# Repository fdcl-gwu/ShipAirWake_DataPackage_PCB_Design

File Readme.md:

# PCB_Design_Two_Anemometers

PCB .sch & .brd files.
Designed using EagleCAD.

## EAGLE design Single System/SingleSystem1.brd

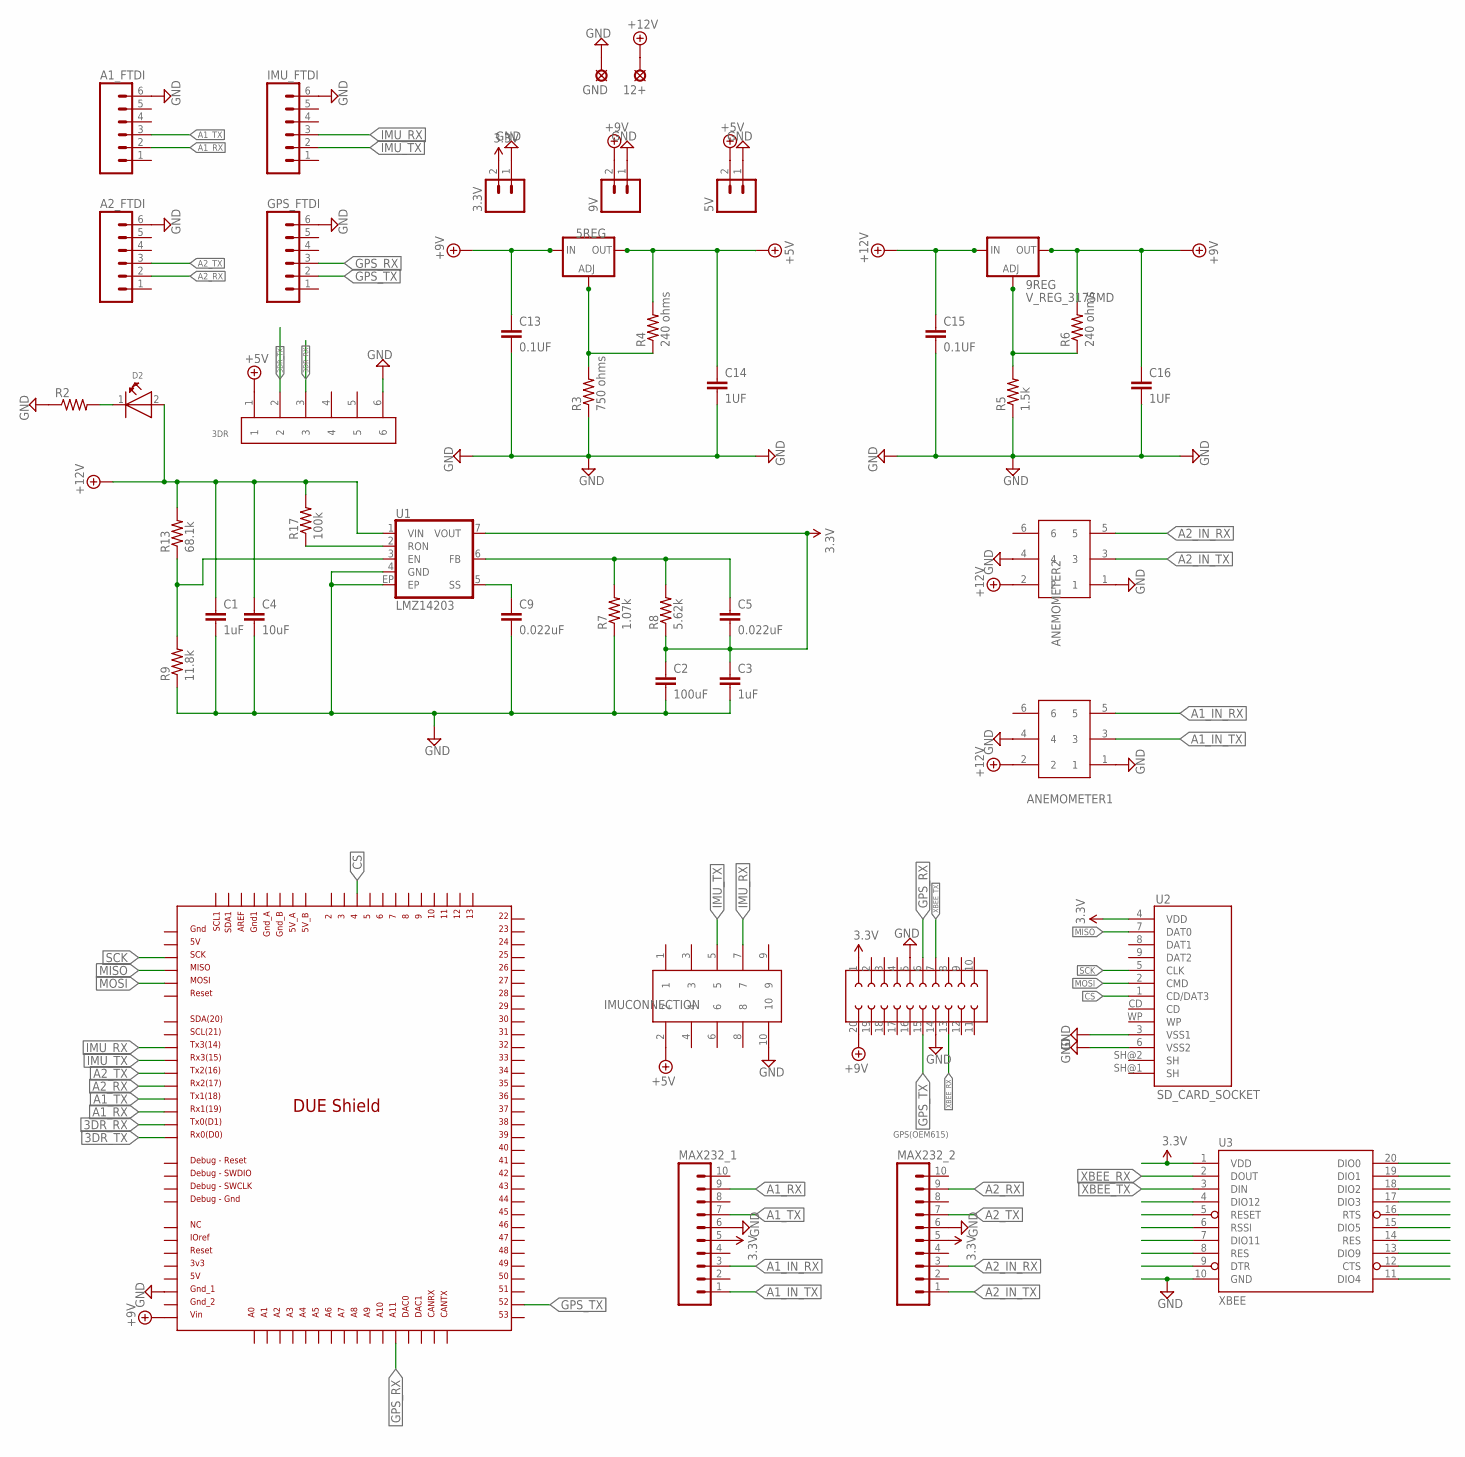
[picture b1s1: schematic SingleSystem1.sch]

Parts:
3.3V, 5V, 9V: M02; 02P
3DR: 653006114822
5REG, 9REG: V_REG_317SMD; SOT223
12+: SE14
A1_FTDI, A2_FTDI: M06; 06P
ANEMOMETER1, ANEMOMETER2: 61200622323
C1, C3: 1uF; 0805; MPN 1C10Z5U104M050R
C2: 100uF; 1206
C4: 10uF; 0805
C5, C9: 0.022uF; 0603-CAP
C13, C15: 0.1UF; 0805
C14, C16: 1UF; 0805
D2: WL-SMCW-150120BS75000-B; 1206
GND: SE14
GPS(OEM615): 62002021821
GPS_FTDI: M06; 06P
IMUCONNECTION: 62501021621
IMU_FTDI: M06; 06P
MAX232_1, MAX232_2: M10; 10P
R2: R-US_M2012; M2012
R3: 750 ohms; M2012
R4, R6: 240 ohms; M2012
R5: 1.5k; M2012
R7: 1.07k; M2012
R8: 5.62k; M2012
R9: 11.8k; M2012
R13: 68.1k; M2012
R17: 100k; M2012
U1: LMZ14203; TO-PMOD-7
U2: SD_CARD_SOCKET; SD_1:1
U3: XBEE; XBEE-1
U$1: DUE(NORMAL)

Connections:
3.3V: 3.3V.2, C2.1, C3.1, C5.2, GPS(OEM615).1, MAX232_1.5, MAX232_2.5, R8.1, U1.7 (VOUT), U2.4 (VDD), U3.1 (VDD)
3DR_RX: 3DR.3, U$1.TX0
3DR_TX: 3DR.2, U$1.RX0
+5V: 3DR.1, 5REG.2 (OUT), 5V.2, C14.1, IMUCONNECTION.2, R4.2
+9V: 5REG.3 (IN), 9REG.2 (OUT), 9V.2, C13.1, C16.1, GPS(OEM615).20, R6.2, U$1.VIN
+12V: 9REG.3 (IN), 12+.MP, ANEMOMETER1.2, ANEMOMETER2.2, C1.1, C4.1, C15.1, D2.2 (A), R13.2, R17.2, U1.1 (VIN)
A1_IN_RX: ANEMOMETER1.5, MAX232_1.3
A1_IN_TX: ANEMOMETER1.3, MAX232_1.1
A1_RX: A1_FTDI.2, MAX232_1.9, U$1.RX1
A1_TX: A1_FTDI.3, MAX232_1.7, U$1.TX1
A2_IN_RX: ANEMOMETER2.5, MAX232_2.3
A2_IN_TX: ANEMOMETER2.3, MAX232_2.1
A2_RX: A2_FTDI.2, MAX232_2.9, U$1.RX2
A2_TX: A2_FTDI.3, MAX232_2.7, U$1.TX2
CS: U2.1 (CD/DAT3), U$1.4
GND: 3.3V.1, 3DR.6, 5V.1, 9V.1, A1_FTDI.6, A2_FTDI.6, ANEMOMETER1.1, ANEMOMETER1.4, ANEMOMETER2.1, ANEMOMETER2.4, C1.2, C2.2, C3.2, C4.2, C9.2, C13.2, C14.2, C15.2, C16.2, GND.MP, GPS(OEM615).5, GPS(OEM615).14, GPS_FTDI.6, IMUCONNECTION.10, IMU_FTDI.6, MAX232_1.6, MAX232_2.6, R2.1, R3.1, R5.1, R7.1, R9.1, U1.4 (GND), U1.EP, U2.3 (VSS1), U2.6 (VSS2), U3.10 (GND), U$1.GND_1
GPS_RX: GPS(OEM615).6, GPS_FTDI.3, U$1.A11
GPS_TX: GPS(OEM615).15, GPS_FTDI.2, U$1.52
IMU_RX: IMUCONNECTION.7, IMU_FTDI.3, U$1.TX3
IMU_TX: IMUCONNECTION.5, IMU_FTDI.2, U$1.RX3
MISO: U2.7 (DAT0), U$1.MISO_ICSP
MOSI: U2.2 (CMD), U$1.MOSI_ICSP
unnamed: 5REG.1 (ADJ), R3.2, R4.1
unnamed: 9REG.1 (ADJ), R5.2, R6.1
unnamed: R9.2, R13.1, U1.3 (EN)
unnamed: R17.1, U1.2 (RON)
unnamed: C9.1, U1.5 (SS)
unnamed: D2.1 (K), R2.2
unnamed: C5.1, R7.2, R8.2, U1.6 (FB)
SCK: U2.5 (CLK), U$1.SCK_ICSP
XBEE_RX: GPS(OEM615).13, U3.2 (DOUT)
XBEE_TX: GPS(OEM615).7, U3.3 (DIN)

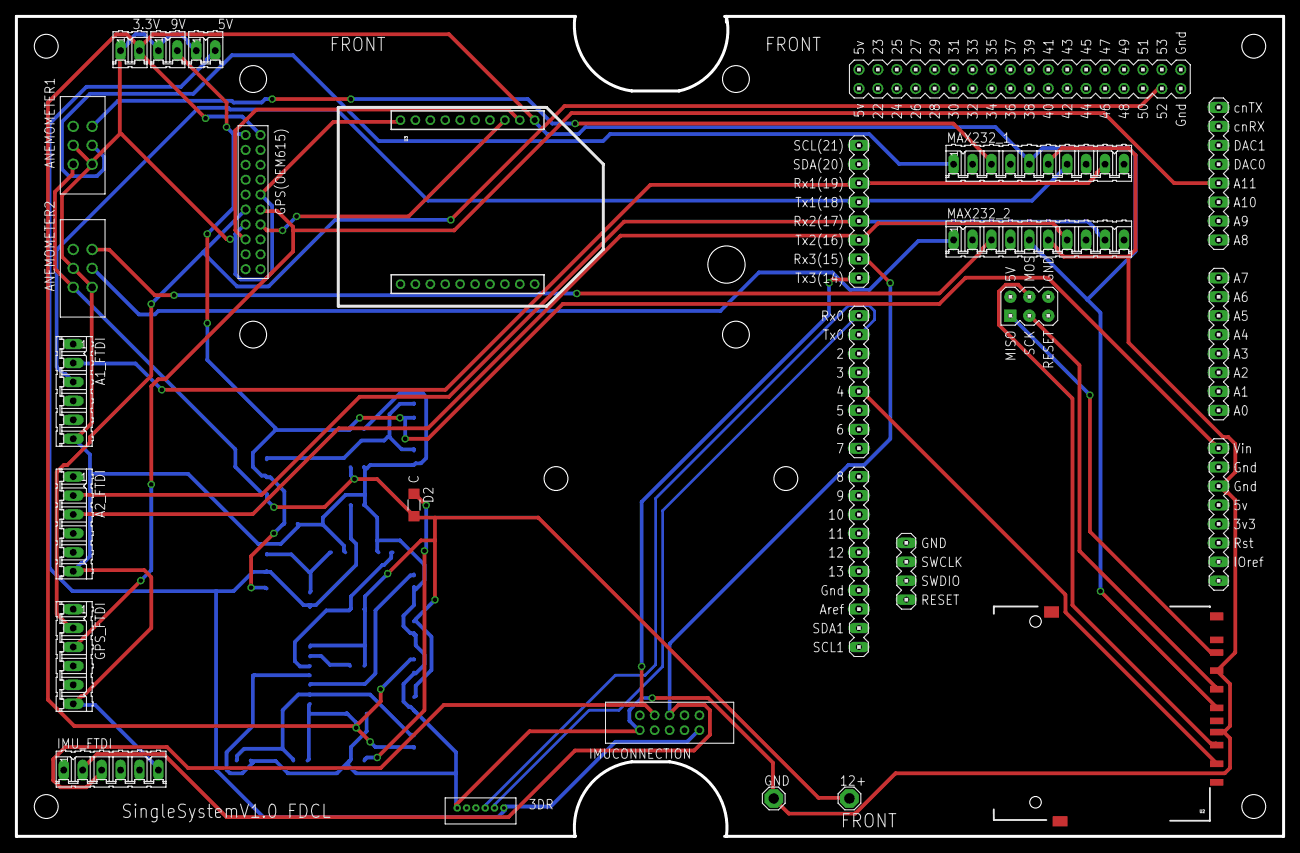
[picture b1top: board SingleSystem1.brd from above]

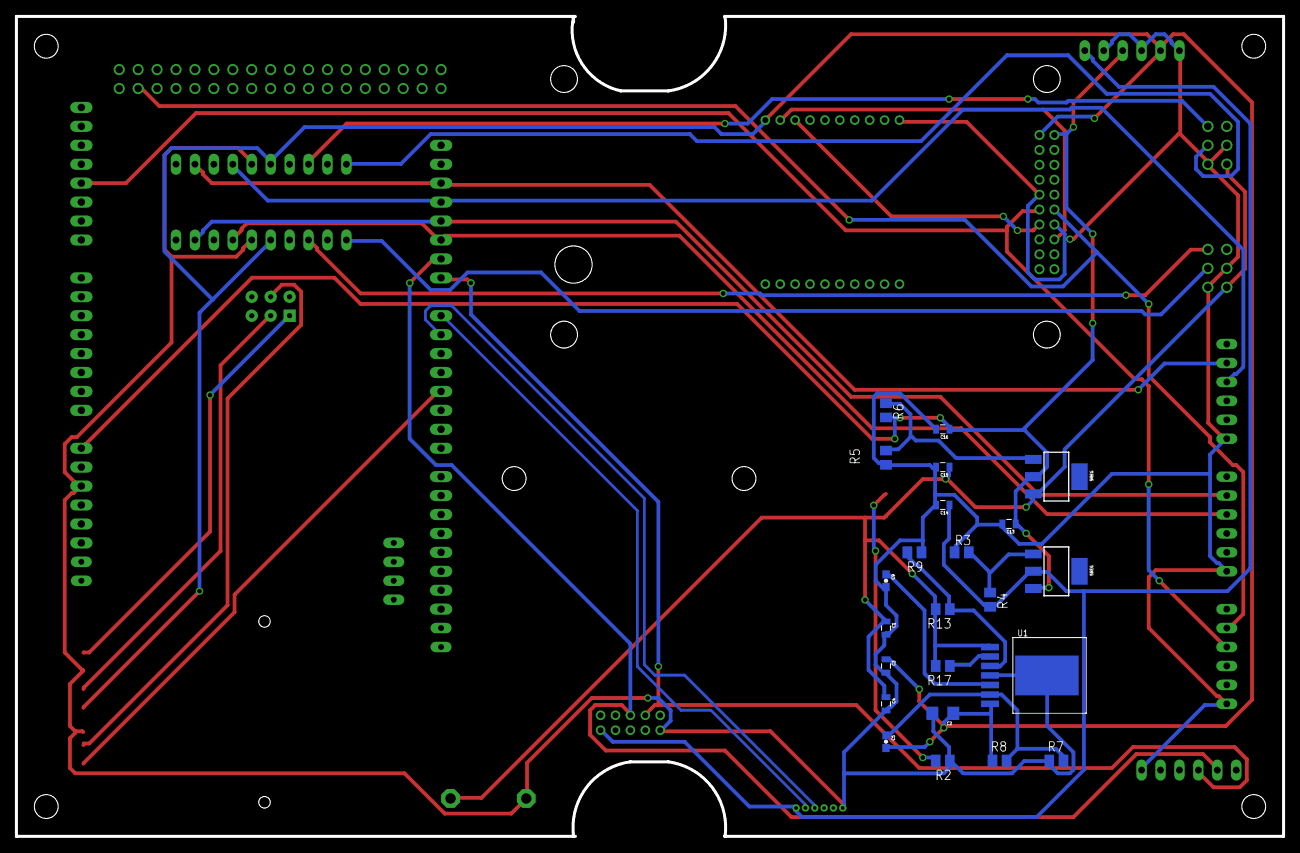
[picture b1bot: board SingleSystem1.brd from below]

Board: 2 copper layers, 170.0 x 110.0 mm, 43 parts (23 on the bottom side), 32 nets.

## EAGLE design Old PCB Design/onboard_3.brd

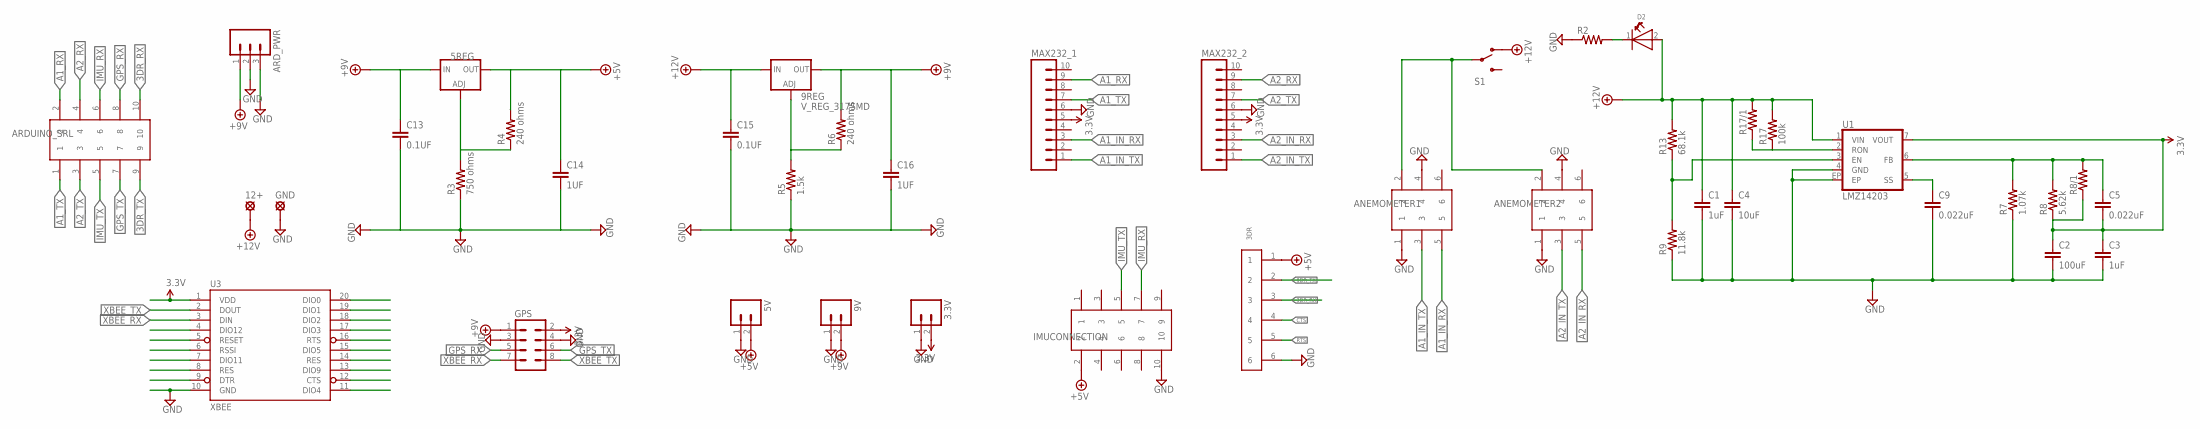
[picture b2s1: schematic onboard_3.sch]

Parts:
3.3V, 5V, 9V: M02; 02P
3DR: 653006114822
5REG, 9REG: V_REG_317SMD; SOT223
12+: SE14
ANEMOMETER1, ANEMOMETER2: 61200622323
ARDUINO_SRL: 61201022323
ARD_PWR: M03; 03P
C1, C3: 1uF; 0805; MPN 1C10Z5U104M050R
C2: 100uF; 1206
C4: 10uF; 0805
C5, C9: 0.022uF; 0603-CAP
C13, C15: 0.1UF; 0805
C14, C16: 1UF; 0805
D2: WL-SMCW-150120BS75000-B; 1206
GND: SE14
GPS: M04X2; 2X4
IMUCONNECTION: 62501021621
MAX232_1, MAX232_2: M10; 10P
R2: R-US_M2012; M2012
R3: 750 ohms; M2012
R4, R6: 240 ohms; M2012
R5: 1.5k; M2012
R7: 1.07k; M2012
R8: 5.62k; M2012
R8/1, R17/1: RESISTORPTH-1/2W; AXIAL-0.5
R9: 11.8k; M2012
R13: 68.1k; M2012
R17: 100k; M2012
S1: SWITCH-SPDTSMD2; SWITCH-SPDT-SMD
U1: LMZ14203; TO-PMOD-7
U3: XBEE; XBEE-1

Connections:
3.3V: 3.3V.2, C2.1, C3.1, C5.2, GPS.2, MAX232_1.5, MAX232_2.5, R8.1, R8/1.P$1 (1), U1.7 (VOUT), U3.1 (VDD)
3DR_RX: 3DR.3, ARDUINO_SRL.10
3DR_TX: 3DR.2, ARDUINO_SRL.9
+5V: 3DR.1, 5REG.2 (OUT), 5V.2, C14.1, IMUCONNECTION.2, R4.2
+9V: 5REG.3 (IN), 9REG.2 (OUT), 9V.2, ARD_PWR.1, C13.1, C16.1, GPS.1, R6.2
+12V: 9REG.3 (IN), 12+.MP, C1.1, C4.1, C15.1, D2.2 (A), R13.2, R17.2, R17/1.P$2 (2), S1.1 (O), U1.1 (VIN)
A1_IN_RX: ANEMOMETER1.5, MAX232_1.3
A1_IN_TX: ANEMOMETER1.3, MAX232_1.1
A1_RX: ARDUINO_SRL.2, MAX232_1.9
A1_TX: ARDUINO_SRL.1, MAX232_1.7
A2_IN_RX: ANEMOMETER2.5, MAX232_2.3
A2_IN_TX: ANEMOMETER2.3, MAX232_2.1
A2_RX: ARDUINO_SRL.4, MAX232_2.9
A2_TX: ARDUINO_SRL.3, MAX232_2.7
CTS: 3DR.4
GND: 3.3V.1, 3DR.6, 5V.1, 9V.1, ANEMOMETER1.1, ANEMOMETER1.4, ANEMOMETER2.1, ANEMOMETER2.4, ARD_PWR.2, ARD_PWR.3, C1.2, C2.2, C3.2, C4.2, C9.2, C13.2, C14.2, C15.2, C16.2, GND.MP, GPS.3, GPS.4, IMUCONNECTION.10, MAX232_1.6, MAX232_2.6, R2.1, R3.1, R5.1, R7.1, R9.1, U1.4 (GND), U1.EP, U3.10 (GND)
GPS_RX: ARDUINO_SRL.8, GPS.5
GPS_TX: ARDUINO_SRL.7, GPS.6
IMU_RX: ARDUINO_SRL.6, IMUCONNECTION.7
IMU_TX: ARDUINO_SRL.5, IMUCONNECTION.5
unnamed: 5REG.1 (ADJ), R3.2, R4.1
unnamed: 9REG.1 (ADJ), R5.2, R6.1
unnamed: R9.2, R13.1, U1.3 (EN)
unnamed: R17.1, R17/1.P$1 (1), U1.2 (RON)
unnamed: C9.1, U1.5 (SS)
unnamed: D2.1 (K), R2.2
unnamed: C5.1, R7.2, R8.2, R8/1.P$2 (2), U1.6 (FB)
unnamed: ANEMOMETER1.2, ANEMOMETER2.2, S1.2
RTS: 3DR.5
XBEE_RX: GPS.7, U3.3 (DIN)
XBEE_TX: GPS.8, U3.2 (DOUT)

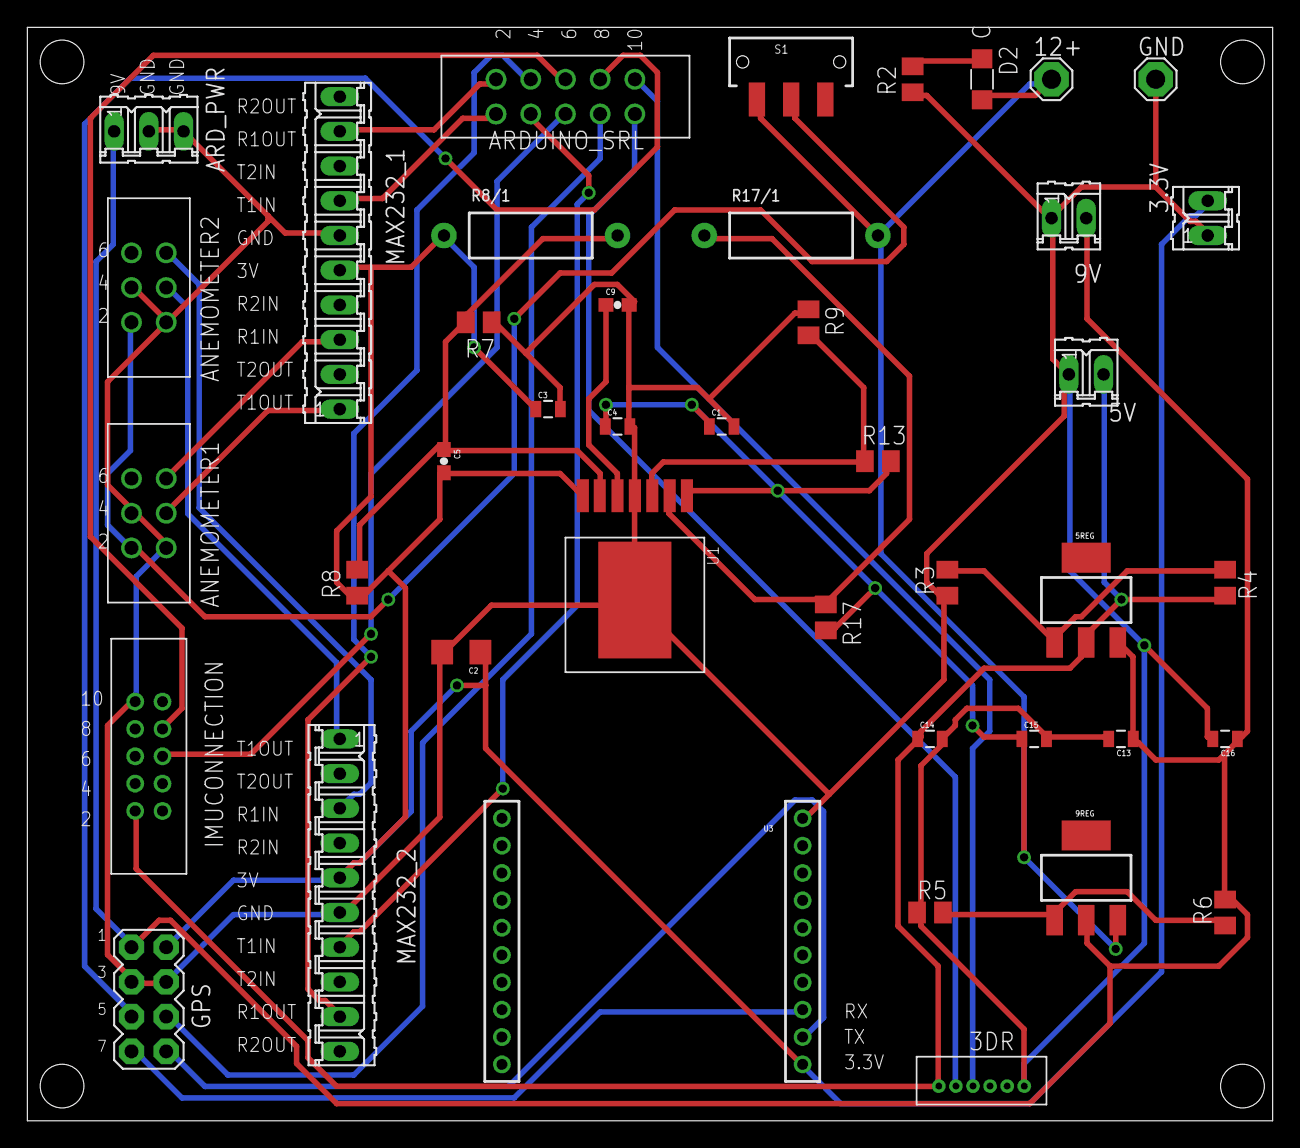
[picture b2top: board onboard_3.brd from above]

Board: 2 copper layers, 91.1 x 80.0 mm, 42 parts (0 on the bottom side), 29 nets.

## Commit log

2016-11-01 update the files from Google drive boardV3
2016-11-01 edited the component list
2016-11-02 started with new PCB design (All in one)
2016-11-03 done, now verifying
2016-11-03 Done, Kanishke will verify
2016-11-03 modified, verification is remaining
2016-11-04 edited the pwr connections
2016-11-04 Renamed the PDF file name
2016-11-04 edited 3DR
2016-11-04 changes to git files
2016-11-04 final done

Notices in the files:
parts and their libraries:
SparkFun-PowerIC: Licensing: Creative Commons ShareAlike 4.0 International - https://creativecommons.org/licenses/by-sa/4.0
Wire_to_Board_Connectors_rev15d: Copyright: Würth Elektronik
